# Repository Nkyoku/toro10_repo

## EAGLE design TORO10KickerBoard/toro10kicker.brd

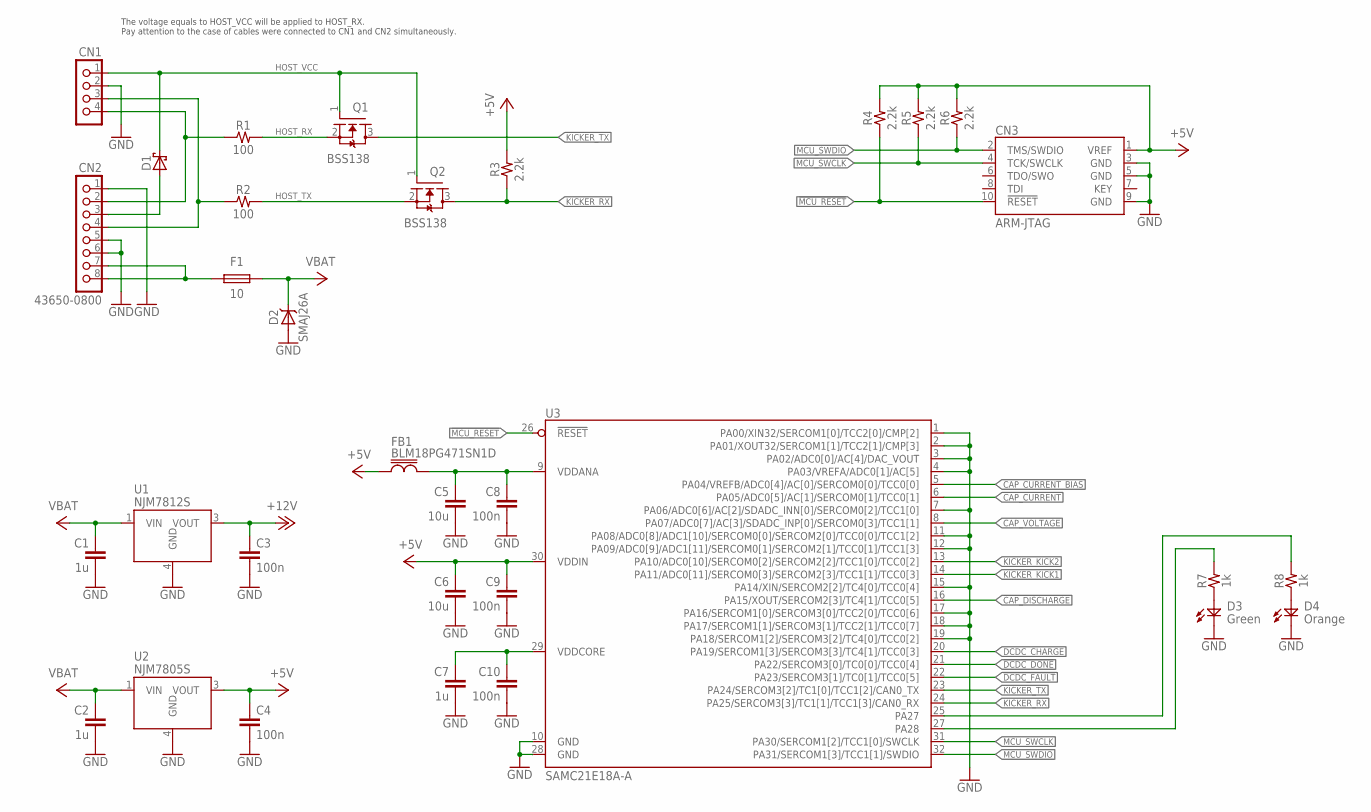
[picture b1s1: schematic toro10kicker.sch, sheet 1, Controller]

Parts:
C1, C2, C7: 1u; 1608
C3, C4, C8, C9, C10: 100n; 1608
C5, C6: 10u; 2012
CN1: PIN1X4
CN2: 43650-0800
CN3: ARM-JTAG; PIN2X5-SMT1.27
D1: SBD-1608; 1608D
D2: SMAJ26A; DO-214AC
D3: Green; 1608D
D4: Orange; 1608D
F1: 10; 3216
FB1: BLM18PG471SN1D; 1608
Q1, Q2: BSS138; SOT23-3
R1, R2: 100; 1608
R3, R4, R5, R6: 2.2k; 1608
R7, R8: 1k; 1608
U1: NJM7812S; DPAK-3
U2: NJM7805S; DPAK-3
U3: SAMC21E18A-A; QFP32-0.8

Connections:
!CAP_DISCHARGE: U3.16 (PA15/XOUT/SERCOM2[3]/TC4[1]/TCC0[5]); also elsewhere on the board
!DCDC_DONE: U3.21 (PA22/SERCOM3[0]/TC0[0]/TCC0[4]); also elsewhere on the board
!DCDC_FAULT: U3.22 (PA23/SERCOM3[1]/TC0[1]/TCC0[5]); also elsewhere on the board
!MCU_RESET: CN3.10 (!RESET), R4.1, U3.26 (!RESET)
+5V: C4.1, C6.1, C9.1, CN3.1 (VREF), FB1.1, R3.2, R4.2, R5.2, R6.2, U2.3 (VOUT), U3.30 (VDDIN); also elsewhere on the board
+12V: C3.1, U1.3 (VOUT); also elsewhere on the board
CAP_CURRENT: U3.6 (PA05/ADC0[5]/AC[1]/SERCOM0[1]/TCC0[1]); also elsewhere on the board
CAP_CURRENT_BIAS: U3.5 (PA04/VREFB/ADC0[4]/AC[0]/SERCOM0[0]/TCC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); also elsewhere on the board
CAP_VOLTAGE: U3.8 (PA07/ADC0[7]/AC[3]/SDADC_INP[0]/SERCOM0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); also elsewhere on the board
DCDC_CHARGE: U3.20 (PA19/SERCOM1[3]/SERCOM3[3]/TC4[1]/TCC0[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); also elsewhere on the board
GND: C1.2, C2.2, C3.2, C4.2, C5.2, C6.2, C7.2, C8.2, C9.2, C10.2, CN1.2, CN2.1, CN2.5, CN2.6, CN3.3 (GND), CN3.5 (GND), CN3.9 (GND), D2.A, D3.K, D4.K, U1.4 (GND), U2.4 (GND), U3.1 (PA00/XIN32/SERCOM1[0]/TCC2[0]/CMP[2]), U3.2 (PA01/XOUT32/SERCOM1[1]/TCC2[1]/CMP[3]), U3.3 (PA02/ADC0[0]/AC[4]/DAC_VOUT), U3.4 (PA03/VREFA/ADC0[1]/AC[5]), U3.7 (PA06/ADC0[6]/AC[2]/SDADC_INN[0]/SERCOM0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), U3.10 (GND), U3.11 (PA08/ADC0[8]/ADC1[10]/SERCOM0[0]/SERCOM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), U3.12 (PA09/ADC0[9]/ADC1[11]/SERCOM0[1]/SERCOM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), U3.15 (PA14/XIN/SERCOM2[2]/TC4[0]/TCC0[4]), U3.17 (PA16/SERCOM1[0]/SERCOM3[0]/TCC2[0]/TCC0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), U3.18 (PA17/SERCOM1[1]/SERCOM3[1]/TCC2[1]/TCC0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), U3.19 (PA18/SERCOM1[2]/SERCOM3[2]/TC4[0]/TCC0[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), U3.28 (GND); also elsewhere on the board
HOST_RX: Q1.2 (S), R1.2
HOST_TX: Q2.2 (S), R2.2
HOST_VCC: CN1.1, D1.K, Q1.1 (G), Q2.1 (G)
KICKER_KICK1: U3.14 (PA11/ADC0[11]/SERCOM0[3]/SERCOM2[3]/TCC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); also elsewhere on the board
KICKER_KICK2: U3.13 (PA10/ADC0[10]/SERCOM0[2]/SERCOM2[2]/TCC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); also elsewhere on the board
KICKER_RX: Q2.3 (D), R3.1, U3.24 (PA25/SERCOM3[3]/TC1[1]/TCC1[3]/CAN0_RX)
KICKER_TX: Q1.3 (D), U3.23 (PA24/SERCOM3[2]/TC1[0]/TCC1[2]/CAN0_TX)
MCU_SWCLK: CN3.4 (TCK/SWCLK), R5.1, U3.31 (PA30/SERCOM1[2]/TCC1[0]/SWCLK)
MCU_SWDIO: CN3.2 (TMS/SWDIO), R6.1, U3.32 (PA31/SERCOM1[3]/TCC1[1]/SWDIO)
unnamed: CN2.7, CN2.8, F1.1
unnamed: C5.1, C8.1, FB1.2, U3.9 (VDDANA)
unnamed: C7.1, C10.1, U3.29 (VDDCORE)
unnamed: CN1.4, CN2.2, R1.1
unnamed: CN1.3, CN2.4, R2.1
unnamed: D3.A, R7.1
unnamed: CN2.3, D1.A
unnamed: D4.A, R8.1
unnamed: R8.2, U3.25 (PA27)
unnamed: R7.2, U3.27 (PA28)
VBAT: C1.1, C2.1, D2.K, F1.2, U1.1 (VIN), U2.1 (VIN); also elsewhere on the board

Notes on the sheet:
The voltage equals to HOST_VCC will be applied to HOST_RX. Pay attention to the case of cables were connected to CN1 and CN2 simultaneously.

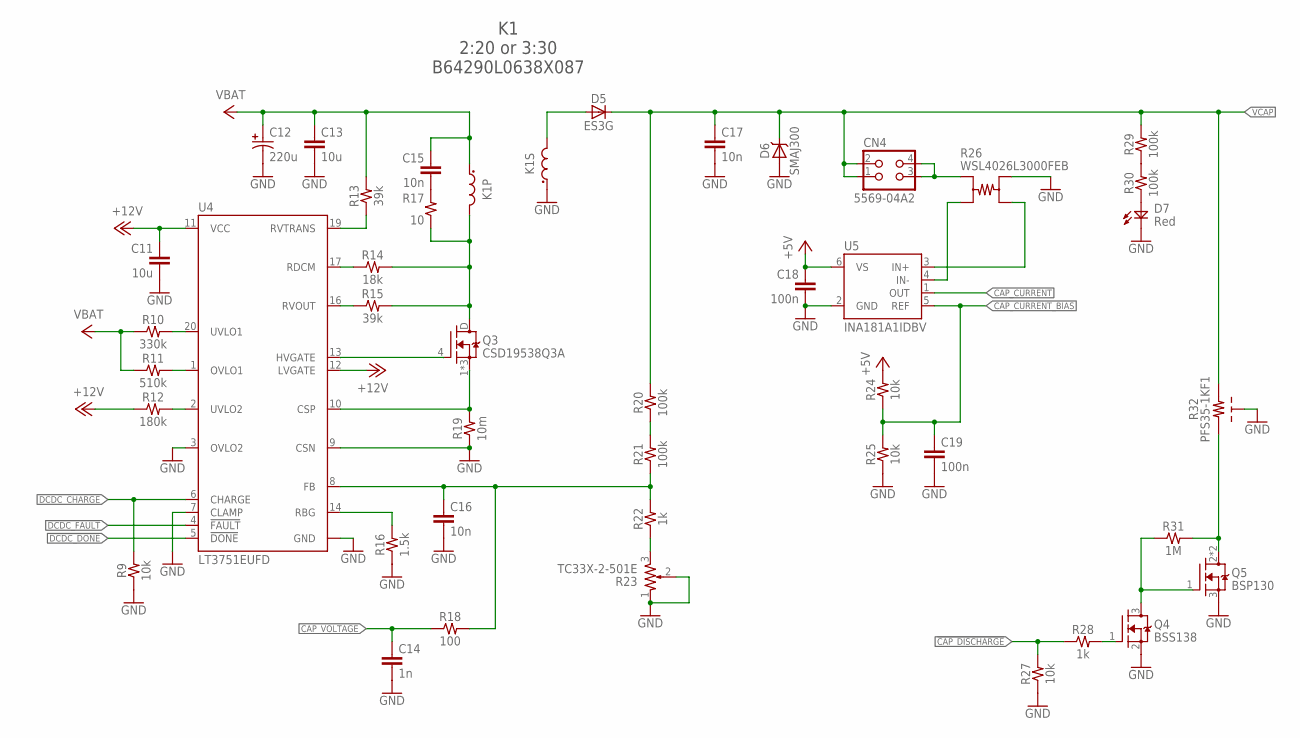
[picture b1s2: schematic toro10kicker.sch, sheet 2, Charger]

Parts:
C11: 10u; 2012
C12: 220u; E3.5-8
C13: 10u; 3225
C14: 1n; 1608
C15, C16: 10n; 1608
C17: 10n; 3225
C18, C19: 100n; 1608
CN4: 5569-04A2
D5: ES3G; DO-214AB
D6: SMAJ300; DO-214AC
D7: Red; 1608D
K1: TRANS; TRANS-23.3X12.6X7.4
Q3: CSD19538Q3A; Q3A
Q4: BSS138; SOT23-3
Q5: BSP130; SOT223
R9, R24, R25, R27: 10k; 1608
R10: 330k; 1608
R11: 510k; 1608
R12: 180k; 1608
R13, R15: 39k; 1608
R14: 18k; 1608
R16: 1.5k; 1608
R17: 10; 3216
R18: 100; 1608
R19: 10m; 3216
R20, R21, R29, R30: 100k; 3216
R22, R28: 1k; 1608
R23: TC33X-2-501E; TC33X
R26: WSL4026L3000FEB; WSL4026
R31: 1M; 3216
R32: PFS35-1KF1; D2PAK-3
U4: LT3751EUFD; QFN20-0.5-4X5
U5: INA181A1IDBV; SOT23-6

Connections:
!CAP_DISCHARGE: R27.2, R28.1; also elsewhere on the board
!DCDC_DONE: U4.5 (!DONE); also elsewhere on the board
!DCDC_FAULT: U4.4 (!FAULT); also elsewhere on the board
+5V: C18.1, R24.2, U5.6 (VS); also elsewhere on the board
+12V: C11.1, R12.1, U4.11 (VCC), U4.12 (LVGATE); also elsewhere on the board
CAP_CURRENT: U5.1 (OUT); also elsewhere on the board
CAP_CURRENT_BIAS: C19.1, R24.1, R25.2, U5.5 (REF); also elsewhere on the board
CAP_VOLTAGE: C14.1, R18.1; also elsewhere on the board
DCDC_CHARGE: R9.2, U4.6 (CHARGE); also elsewhere on the board
GND: C11.2, C12.N, C13.2, C14.2, C16.2, C17.2, C18.2, C19.2, D6.A, D7.K, K1.2A (1), Q4.2 (S), Q5.3 (S), R9.1, R16.1, R19.1, R23.1 (A), R23.2 (W), R25.1, R26.1A, R27.1, R32.4 (S), U4.3 (OVLO2), U4.7 (CLAMP), U4.9 (CSN), U4.PAD (GND), U5.2 (GND); also elsewhere on the board
unnamed: Q3.1 (S), Q3.2 (S), Q3.3 (S), R19.2, U4.10 (CSP)
unnamed: R10.2, U4.20 (UVLO1)
unnamed: R11.2, U4.1 (OVLO1)
unnamed: R12.2, U4.2 (UVLO2)
unnamed: Q5.2 (D), Q5.4 (D), R31.2, R32.1
unnamed: R14.1, U4.17 (RDCM)
unnamed: R15.1, U4.16 (RVOUT)
unnamed: K1.1B (2), Q3.D, R14.2, R15.2, R17.1
unnamed: R13.1, U4.19 (RVTRANS)
unnamed: Q3.4 (G), U4.13 (HVGATE)
unnamed: R22.1, R23.3 (B)
unnamed: C16.1, R18.2, R21.1, R22.2, U4.8 (FB)
unnamed: R16.2, U4.14 (RBG)
unnamed: CN4.3, CN4.4, R26.2A
unnamed: R29.1, R30.2
unnamed: D5.A, K1.2B (2)
unnamed: R20.1, R21.2
unnamed: Q4.3 (D), Q5.1 (G), R31.1
unnamed: C15.2, R17.2
unnamed: Q4.1 (G), R28.2
unnamed: D7.A, R30.1
unnamed: R26.2B, U5.4 (IN-)
unnamed: R26.1B, U5.3 (IN+)
VBAT: C12.P, C13.1, C15.1, K1.1A (1), R10.1, R11.1, R13.2; also elsewhere on the board
VCAP: C17.1, CN4.1, CN4.2, D5.K, D6.K, R20.2, R29.2, R32.3 (2); also elsewhere on the board

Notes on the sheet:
K1 2:20 or 3:30 B64290L0638X087

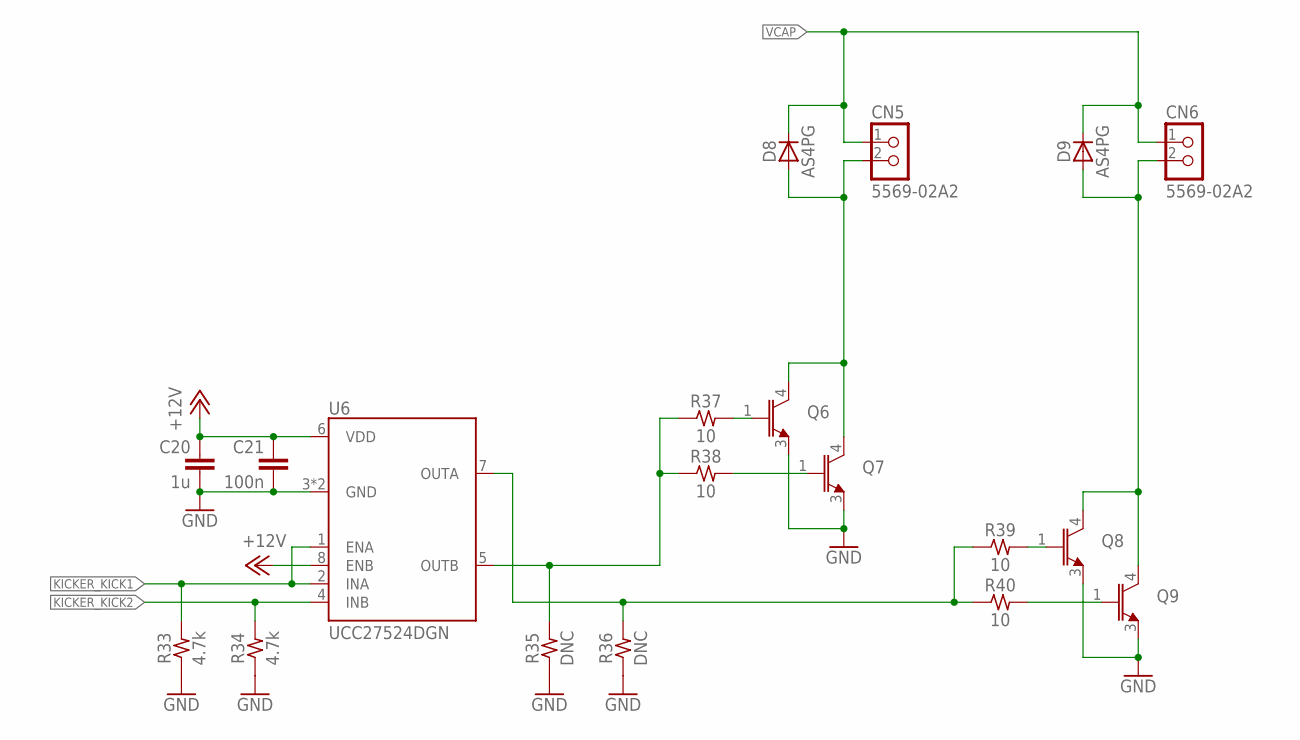
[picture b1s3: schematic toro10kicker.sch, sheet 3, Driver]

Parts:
C20: 1u; 1608
C21: 100n; 1608
CN5, CN6: 5569-02A2
D8, D9: AS4PG; SMPC
Q6, Q7, Q8, Q9: IGBT-N-D2PAK; D2PAK-3
R33, R34: 4.7k; 1608
R35, R36: DNC; 1608
R37, R38, R39, R40: 10; 2012
U6: UCC27524DGN; MSOP8-PAD

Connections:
+12V: C20.1, C21.1, U6.6 (VDD), U6.8 (ENB); also elsewhere on the board
GND: C20.2, C21.2, Q6.3 (E), Q7.3 (E), Q8.3 (E), Q9.3 (E), R33.1, R34.1, R35.1, R36.1, U6.3 (GND), U6.PAD (GND); also elsewhere on the board
KICKER_KICK1: R33.2, U6.1 (ENA), U6.2 (INA); also elsewhere on the board
KICKER_KICK2: R34.2, U6.4 (INB); also elsewhere on the board
unnamed: CN5.2, D8.1 (A), D8.2 (A), Q6.4 (C), Q7.4 (C)
unnamed: CN6.2, D9.1 (A), D9.2 (A), Q8.4 (C), Q9.4 (C)
unnamed: Q6.1 (G), R37.2
unnamed: Q7.1 (G), R38.2
unnamed: R35.2, R37.1, R38.1, U6.5 (OUTB)
unnamed: Q8.1 (G), R39.2
unnamed: Q9.1 (G), R40.2
unnamed: R36.2, R39.1, R40.1, U6.7 (OUTA)
VCAP: CN5.1, CN6.1, D8.K, D9.K; also elsewhere on the board

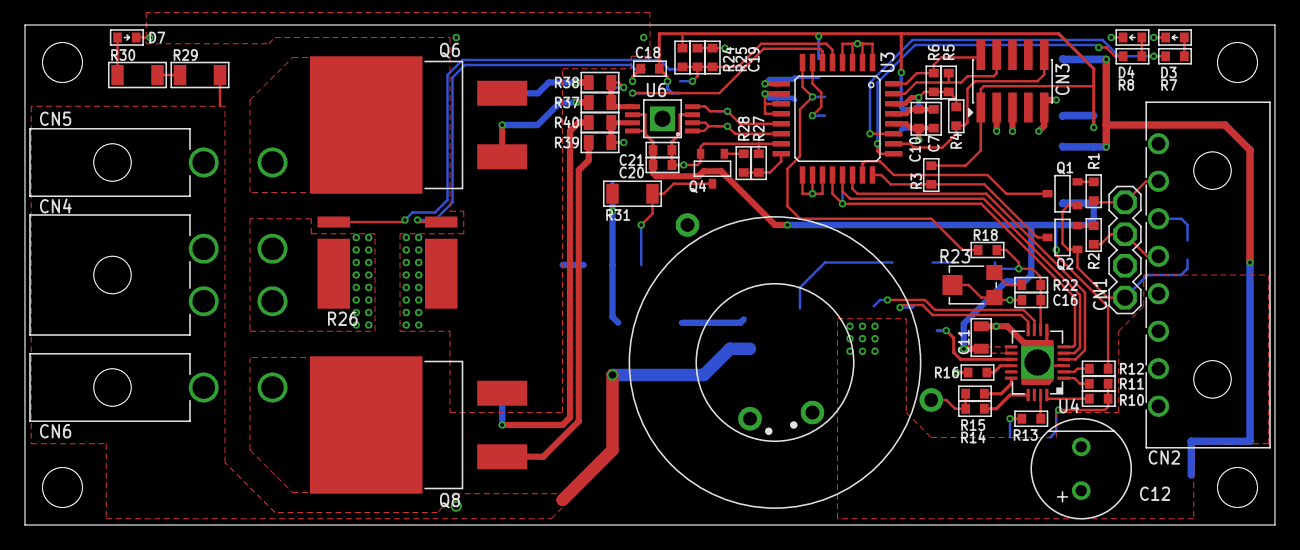
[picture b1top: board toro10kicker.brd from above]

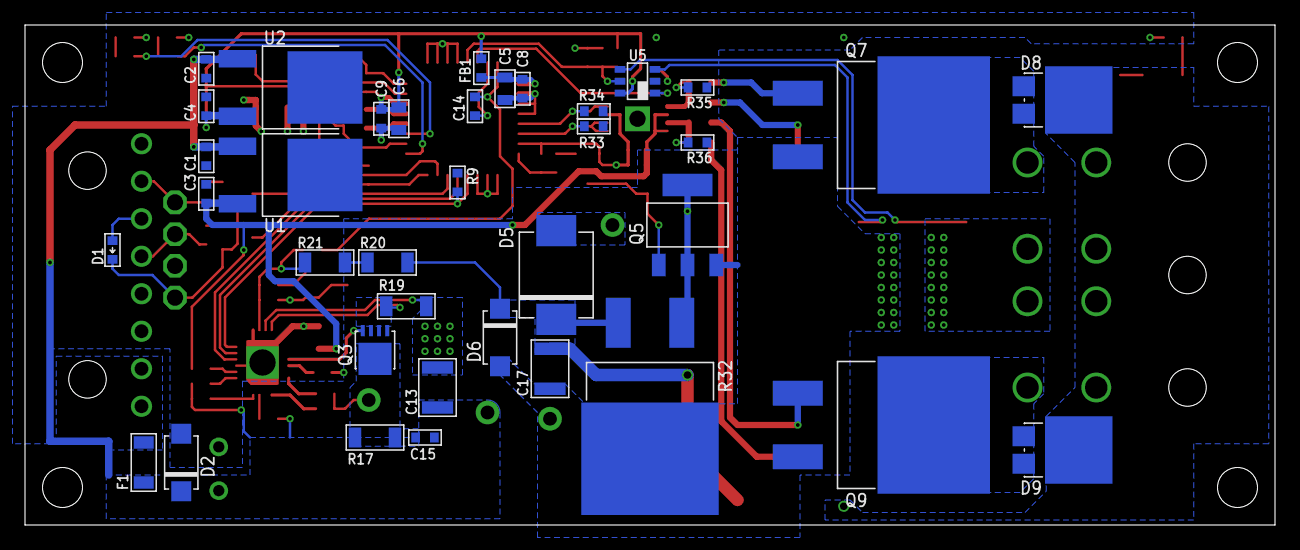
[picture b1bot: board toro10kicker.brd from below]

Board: 2 copper layers, 100.0 x 40.0 mm, 94 parts (37 on the bottom side), 63 nets.

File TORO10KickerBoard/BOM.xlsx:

Device | Model Number | Value | Package | Qty | Parts
Resistor | WSL4026L3000FEB | 0.3mΩ | WSL4026 | 1 | R26
Resistor |  | 10mΩ | 3216 | 1 | R19
Resistor |  | 10Ω | 2012 | 4 | R37, R38, R39, R40
Resistor |  | 10Ω | 3216 | 1 | R17
Resistor |  | 100Ω | 1608 | 3 | R1, R2, R18
Resistor |  | 1kΩ | 1608 | 4 | R7, R8, R22, R28
Resistor | PFS35-1KF1 | 1kΩ | D2PAK-3 | 1 | R32
Resistor |  | 1.5kΩ | 1608 | 1 | R16
Resistor |  | 2.2kΩ | 1608 | 4 | R3, R4, R5, R6
Resistor |  | 4.7kΩ | 1608 | 2 | R33, R34
Resistor |  | 10kΩ | 1608 | 4 | R9, R24, R25, R27
Resistor |  | 18kΩ ±1% | 1608 | 1 | R14
Resistor |  | 39kΩ ±1% | 1608 | 2 | R13, R15
Resistor | KTR18EZPF1003 | 100kΩ ±1% | 3216 | 4 | R20, R21, R29, R30
Resistor |  | 180kΩ ±1% | 1608 | 1 | R12
Resistor |  | 330kΩ ±1% | 1608 | 1 | R10
Resistor |  | 510kΩ ±1% | 1608 | 1 | R11
Resistor | KTR18EZPF1004 | 1MΩ | 3216 | 1 | R31
Resistor |  | Do Not Mount | 1608 | 2 | R35, R36
Potentiometer | TC33X-2-501E | 500Ω | TC33X | 1 | R23
Ceramic Capacitor |  | 1nF | 1608 | 1 | C14
Ceramic Capacitor |  | 10nF | 1608 | 2 | C15, C16
Ceramic Capacitor | GRM31BR72J103KW01L | 10nF 630V | 3225 | 1 | C17
Ceramic Capacitor |  | 100nF | 1608 | 8 | C3, C4, C8, C9, C10, C18, C19, C21
Ceramic Capacitor |  | 1uF | 1608 | 4 | C1, C2, C7, C20
Ceramic Capacitor | GRM21BB31E106KA | 10uF 16V | 2012 | 3 | C5, C6, C11
Ceramic Capacitor | GRM32ER7YA106KA12 | 10uF 35V | 3225 | 1 | C13
Aluminum Capacitor | 35ZLH220MEFCCT8X11.5 | 220uF | φ8mm | 1 | C12
Transformer | B64290L0638X087 |  | TRANS-23.3X12.6X7.4 | 1 | K1
Fuse | 0501010.WR | 10A | 3216 | 1 | F1
Ferrite Bead | BLM18PG471SN1D |  | 1608 | 1 | FB1
Silicon Diode | ES3G-E3/57T |  | DO-214AB | 1 | D5
Silicon Diode | AS4PG-M3/86A |  | SMPC | 2 | D8, D9
Schottky Diode | RB520S-30 |  | 1608 | 1 | D1
TVS Diode | SMAJ26A |  | DO-214AC | 1 | D2
TVS Diode | SMAJ300A |  | DO-214AC | 1 | D6
LED |  | Red | 1608 | 1 | D7
LED |  | Green | 1608 | 2 | D3
LED |  | Orange | 1608 | 2 | D4
Nch MOSFET | BSS138 |  | SOT23-3 | 3 | Q1, Q2, Q4
Nch MOSFET | BSP130,115 |  | SOT223 | 1 | Q5
Nch MOSFET | CSD19538Q3A |  | Q3A | 1 | Q3
IGBT |  |  | D2PAK-3 | 4 | Q6, Q7, Q8, Q9
Linear Regulator | NJM7805SDL1 |  | DPAK-3 | 1 | U2
Linear Regulator | NJM7812SDL1 |  | DPAK-3 | 1 | U1
Boost Regulator | LT3751EUFD#PBF |  | QFN20-0.5-4X5 | 1 | U4
Current Sense Amplifier | INA181A1IDBVT |  | SOT23-6 | 1 | U5
Gate Driver | UCC27524DGNR, UCC27524ADGNR |  | MSOP8-PAD | 1 | U6
Microcontroller | ATSAMC21E18A-AUT |  | QFP32-0.8 | 1 | U3
Header | 0436500800 |  | 43650-0800 | 1 | CN2
Header | 0039301020 |  | 5569-02A2 | 2 | CN5, CN6
Header | 0039301040 |  | 5569-04A2 | 1 | CN4
Pin Header | Pin Header 1x4 2.54mm Pitch |  | PIN1X4 | 1 | CN1
Pin Header | Pin Header 2x5 1.27mm Pitch |  | PIN2X5-SMT1.27 | 1 | CN3

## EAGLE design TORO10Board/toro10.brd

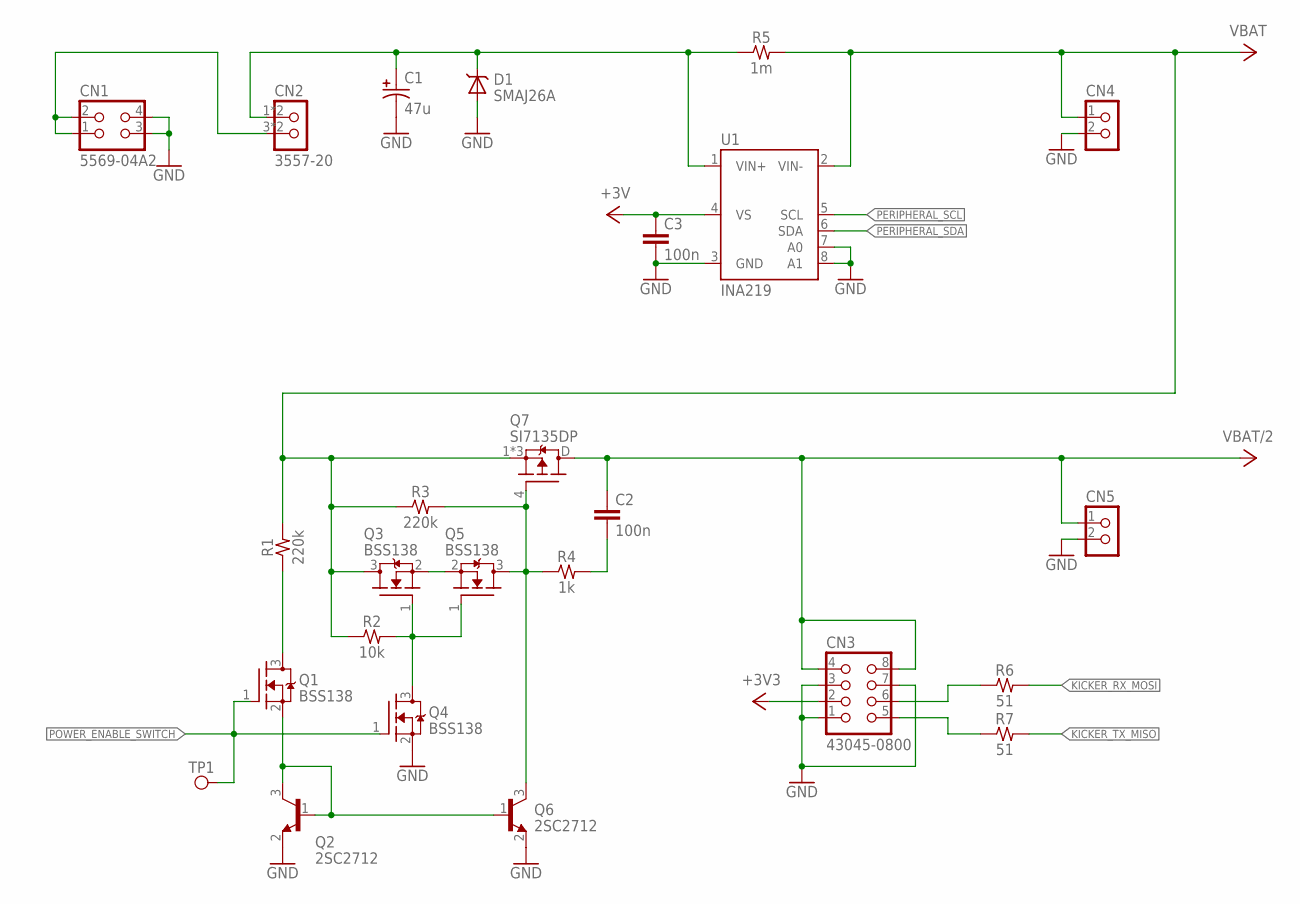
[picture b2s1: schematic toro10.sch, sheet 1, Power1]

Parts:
C1: 47u; E2-5
C2, C3: 100n; 1608
CN1: 5569-04A2
CN2: 3557-20; 3557
CN3: 43045-0800
CN4, CN5: PIN1X2
D1: SMAJ26A; DO-214AC
Q1, Q3, Q4, Q5: BSS138; SOT23-3
Q2, Q6: 2SC2712; SOT23-3
Q7: SI7135DP; POWERPAK-SO-8-S
R1, R3: 220k; 1608
R2: 10k; 1608
R4: 1k; 1608
R5: 1m; WSLF2512
R6, R7: 51; 1608
TP1: TESTPAD-SMT
U1: INA219; SOT23-8

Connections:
+3V: C3.1, U1.4 (VS); also elsewhere on the board
+3V3: CN3.2; also elsewhere on the board
GND: C1.N, C3.2, CN1.3, CN1.4, CN3.1, CN3.3, CN3.7, CN4.2, CN5.2, D1.A, Q2.2 (E), Q4.2 (S), Q6.2 (E), U1.3 (GND), U1.7 (A0), U1.8 (A1); also elsewhere on the board
KICKER_RX_MOSI: R6.2; also elsewhere on the board
KICKER_TX_MISO: R7.2; also elsewhere on the board
unnamed: CN1.1, CN1.2, CN2.3 (2), CN2.4 (2)
unnamed: Q3.2 (S), Q5.2 (S)
unnamed: Q3.1 (G), Q4.3 (D), Q5.1 (G), R2.2
unnamed: Q1.2 (S), Q2.1 (B), Q2.3 (C), Q6.1 (B)
unnamed: Q5.3 (D), Q6.3 (C), Q7.4 (G), R3.2, R4.1
unnamed: C2.2, R4.2
unnamed: Q1.3 (D), R1.1
unnamed: C1.P, CN2.1, CN2.2 (1), D1.K, R5.1, U1.1 (VIN+)
unnamed: CN3.6, R6.1
unnamed: CN3.5, R7.1
PERIPHERAL_SCL: U1.5 (SCL); also elsewhere on the board
PERIPHERAL_SDA: U1.6 (SDA); also elsewhere on the board
POWER_ENABLE_SWITCH: Q1.1 (G), Q4.1 (G), TP1.1; also elsewhere on the board
VBAT: CN4.1, Q3.3 (D), Q7.1 (S), Q7.2 (S), Q7.3 (S), R1.2, R2.1, R3.1, R5.2, U1.2 (VIN-); also elsewhere on the board
VBAT/2: C2.1, CN3.4, CN3.8, CN5.1, Q7.D; also elsewhere on the board

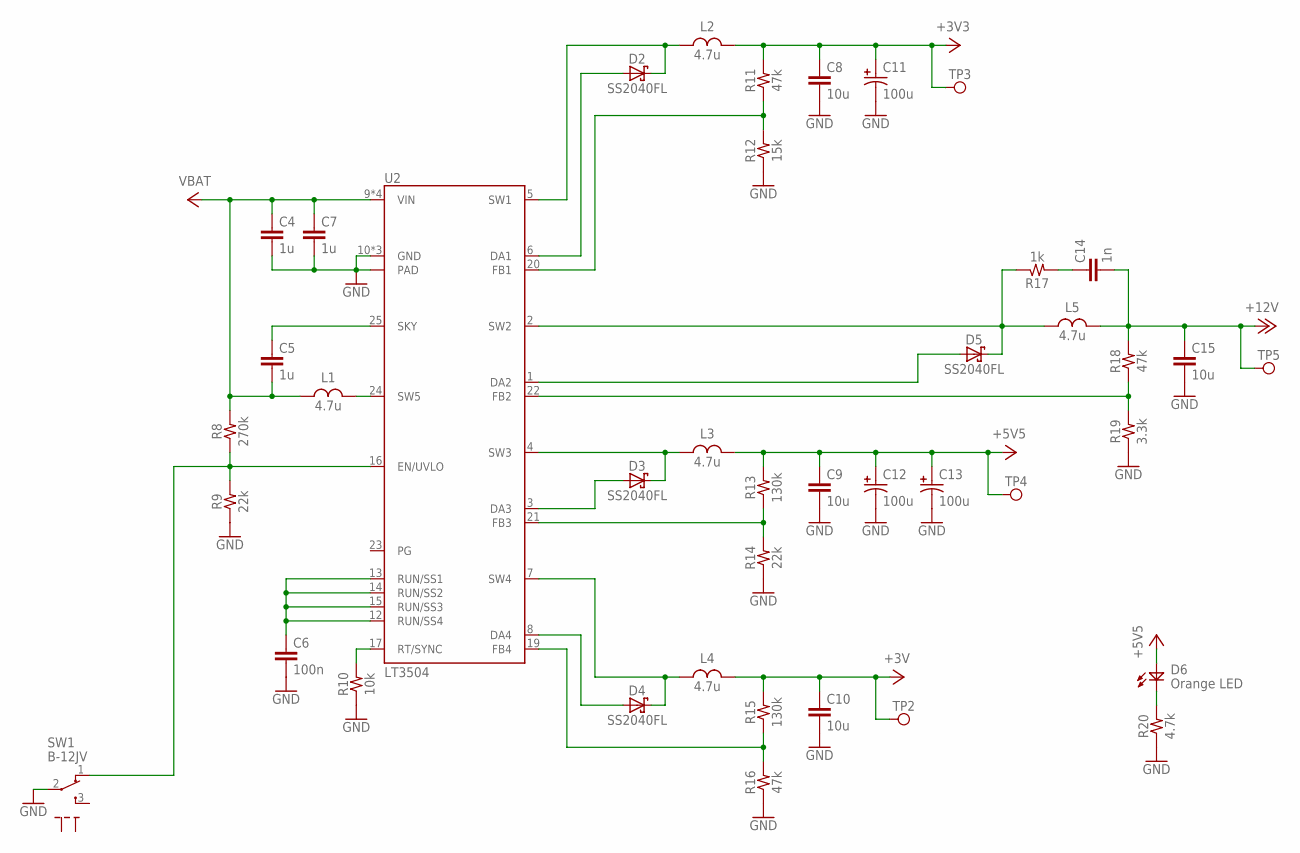
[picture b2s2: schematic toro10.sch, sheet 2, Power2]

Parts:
C4, C5, C7: 1u; 1608
C6: 100n; 1608
C8, C9, C10, C15: 10u; 2012
C11, C12, C13: 100u; E2-5
C14: 1n; 1608
D2, D3, D4, D5: SS2040FL; SOD123
D6: Orange LED; 1608D
L1, L2, L3, L4, L5: 4.7u; MAMK2520
R8: 270k; 1608
R9, R14: 22k; 1608
R10: 10k; 1608
R11, R16, R18: 47k; 1608
R12: 15k; 1608
R13, R15: 130k; 1608
R17: 1k; 1608
R19: 3.3k; 1608
R20: 4.7k; 1608
SW1: B-12JV
TP2, TP3, TP4, TP5: TESTPAD-TH
U2: LT3504; QFN28-0.5

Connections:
+3V: C10.1, L4.2, R15.2, TP2.1; also elsewhere on the board
+3V3: C8.1, C11.P, L2.2, R11.2, TP3.1; also elsewhere on the board
+5V5: C9.1, C12.P, C13.P, D6.A, L3.2, R13.2, TP4.1; also elsewhere on the board
+12V: C14.2, C15.1, L5.2, R18.2, TP5.1; also elsewhere on the board
GND: C4.2, C6.2, C7.2, C8.2, C9.2, C10.2, C11.N, C12.N, C13.N, C15.2, R9.1, R10.1, R12.1, R14.1, R16.1, R19.1, R20.1, SW1.2 (COM), U2.10 (GND), U2.18 (GND), U2.27 (GND), U2.PAD; also elsewhere on the board
unnamed: R18.1, R19.2, U2.22 (FB2)
unnamed: L1.2, U2.24 (SW5)
unnamed: C6.1, U2.12 (RUN/SS4), U2.13 (RUN/SS1), U2.14 (RUN/SS2), U2.15 (RUN/SS3)
unnamed: R10.2, U2.17 (RT/SYNC)
unnamed: C5.1, U2.25 (SKY)
unnamed: D2.K, L2.1, U2.5 (SW1)
unnamed: D5.K, L5.1, R17.1, U2.2 (SW2)
unnamed: R8.1, R9.2, SW1.1 (A), U2.16 (EN/UVLO)
unnamed: R15.1, R16.2, U2.19 (FB4)
unnamed: R11.1, R12.2, U2.20 (FB1)
unnamed: D5.A, U2.1 (DA2)
unnamed: R13.1, R14.2, U2.21 (FB3)
unnamed: D3.A, U2.3 (DA3)
unnamed: D3.K, L3.1, U2.4 (SW3)
unnamed: D4.K, L4.1, U2.7 (SW4)
unnamed: D4.A, U2.8 (DA4)
unnamed: C14.1, R17.2
unnamed: D2.A, U2.6 (DA1)
unnamed: D6.K, R20.2
VBAT: C4.1, C5.2, C7.1, L1.1, R8.2, U2.9 (VIN), U2.11 (VIN), U2.26 (VIN), U2.28 (VIN); also elsewhere on the board

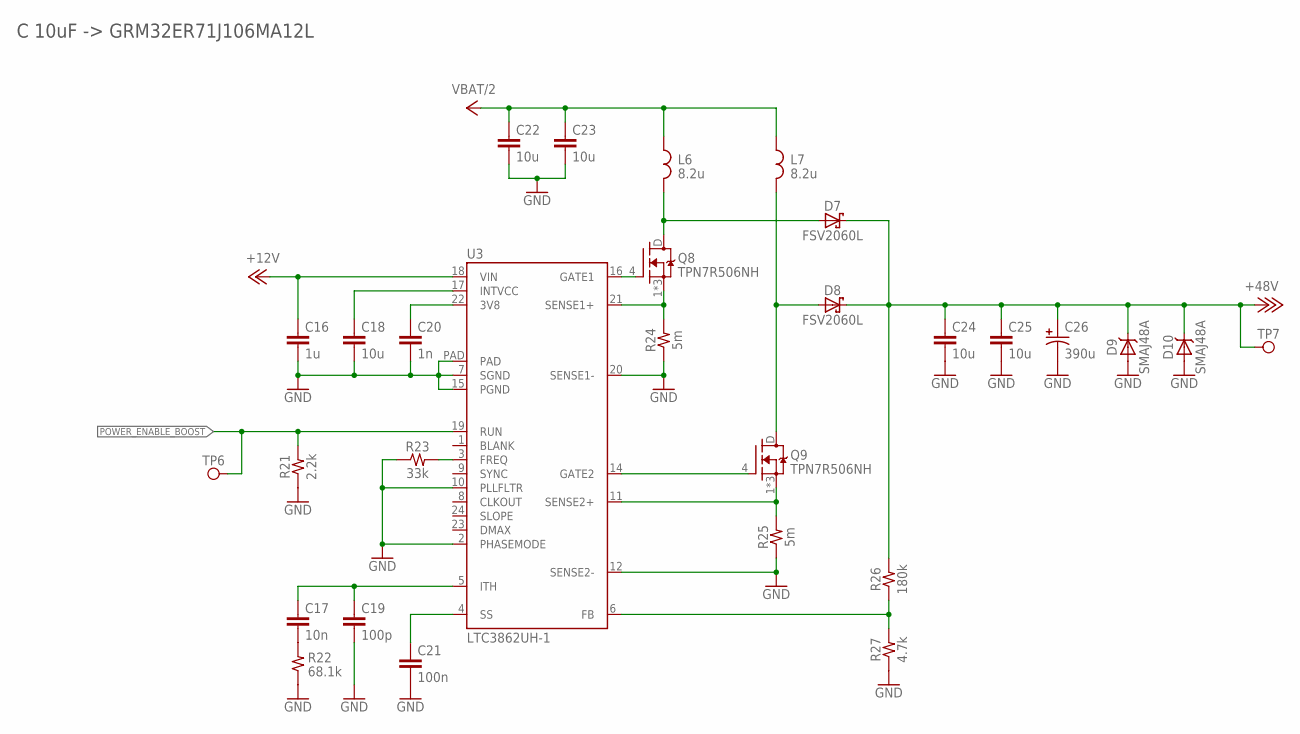
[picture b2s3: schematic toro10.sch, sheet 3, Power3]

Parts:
C16: 1u; 1608
C17: 10n; 1608
C18: 10u; 2012
C19: 100p; 1608
C20: 1n; 1608
C21: 100n; 1608
C22, C23, C24, C25: 10u; 3225
C26: 390u; E7.5-18
D7, D8: FSV2060L; TO-277-3
D9, D10: SMAJ48A; DO-214AC
L6, L7: 8.2u; L-VISHAY-ER
Q8, Q9: TPN7R506NH; TSON-8_3.3
R21: 2.2k; 1608
R22: 68.1k; 1608
R23: 33k; 1608
R24, R25: 5m; 3216WL
R26: 180k; 1608
R27: 4.7k; 1608
TP6, TP7: TESTPAD-SMT
U3: LTC3862UH-1; QFN24-0.65

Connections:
+12V: C16.1, U3.18 (VIN); also elsewhere on the board
+48V: C24.1, C25.1, C26.P, D7.3 (K), D8.3 (K), D9.K, D10.K, R26.2, TP7.1; also elsewhere on the board
GND: C16.2, C18.2, C19.2, C20.2, C21.2, C22.2, C23.2, C24.2, C25.2, C26.N, D9.A, D10.A, R21.1, R22.1, R23.1, R24.1, R25.1, R27.1, U3.2 (PHASEMODE), U3.7 (SGND), U3.10 (PLLFLTR), U3.12 (SENSE2-), U3.15 (PGND), U3.20 (SENSE1-), U3.PAD; also elsewhere on the board
unnamed: Q8.1 (S), Q8.2 (S), Q8.3 (S), R24.2, U3.21 (SENSE1+)
unnamed: C18.1, U3.17 (INTVCC)
unnamed: Q8.4 (G), U3.16 (GATE1)
unnamed: D7.1 (A), D7.2 (A), L6.2, Q8.D
unnamed: Q9.1 (S), Q9.2 (S), Q9.3 (S), R25.2, U3.11 (SENSE2+)
unnamed: C20.1, U3.22 (3V8)
unnamed: Q9.4 (G), U3.14 (GATE2)
unnamed: D8.1 (A), D8.2 (A), L7.2, Q9.D
unnamed: R26.1, R27.2, U3.6 (FB)
unnamed: C21.1, U3.4 (SS)
unnamed: C17.2, R22.2
unnamed: C17.1, C19.1, U3.5 (ITH)
unnamed: R23.2, U3.3 (FREQ)
POWER_ENABLE_BOOST: R21.2, TP6.1, U3.19 (RUN); also elsewhere on the board
VBAT/2: C22.1, C23.1, L6.1, L7.1; also elsewhere on the board

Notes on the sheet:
C 10uF -> GRM32ER71J106MA12L

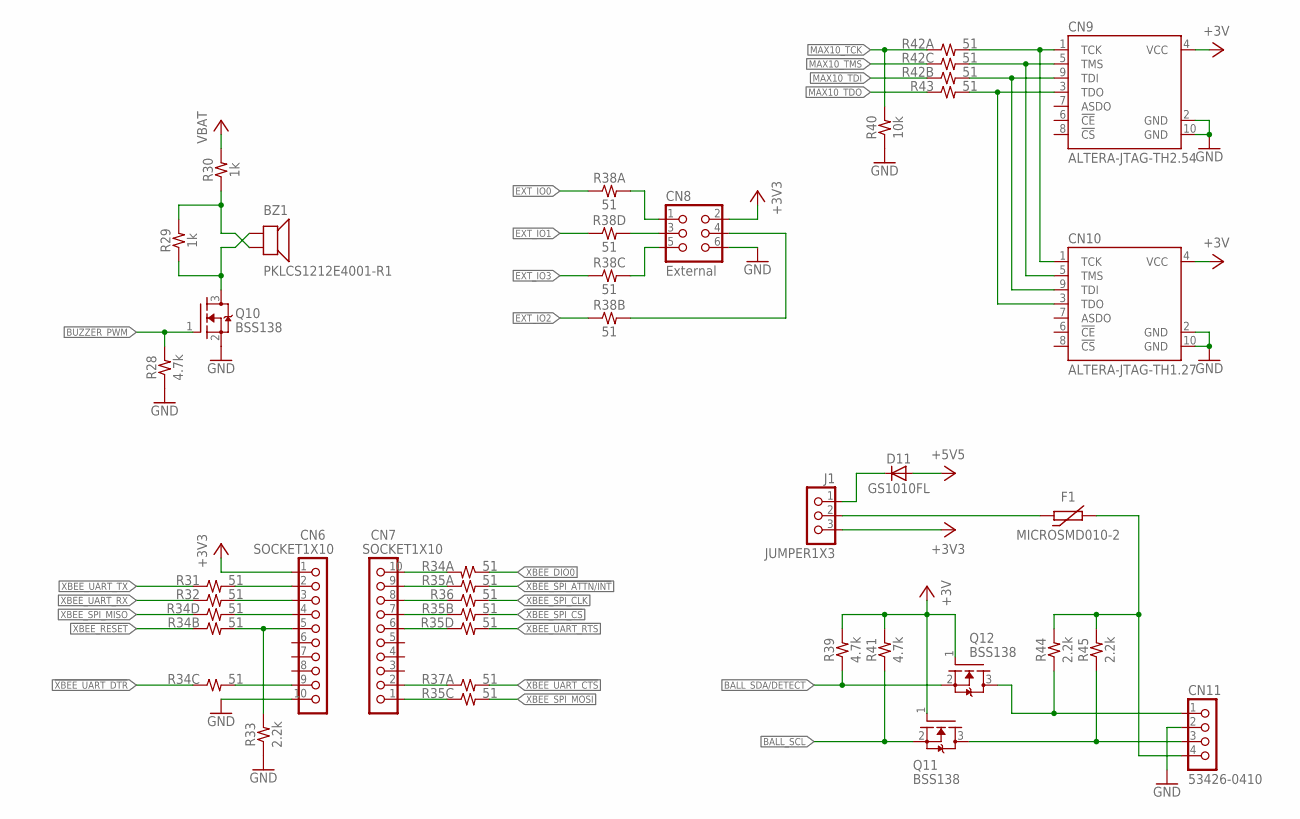
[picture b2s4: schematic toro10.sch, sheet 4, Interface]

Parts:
BZ1: PKLCS1212E4001-R1; PKLCS1212
CN6, CN7: SOCKET1X10; SOCKET1X10-TH2.0
CN8: External; PIN2X3
CN9: ALTERA-JTAG-TH2.54; PIN2X5
CN10: ALTERA-JTAG-TH1.27; PIN2X5-1.27
CN11: 53426-0410; 53426-04
D11: GS1010FL; SOD123
F1: MICROSMD010-2; 3225
J1: JUMPER1X3; PIN1X3
Q10, Q11, Q12: BSS138; SOT23-3
R28, R39, R41: 4.7k; 1608
R29, R30: 1k; 1608
R31, R32, R36, R43: 51; 1608
R33, R44, R45: 2.2k; 1608
R34, R35, R37, R38, R42: 51; 1608-4A
R40: 10k; 1608

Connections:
!XBEE_RESET: R34.B1 (1); also elsewhere on the board
!XBEE_SPI_ATTN/INT: R35.A2 (2); also elsewhere on the board
!XBEE_SPI_CS: R35.B2 (2); also elsewhere on the board
!XBEE_UART_CTS: R37.A2 (2); also elsewhere on the board
!XBEE_UART_DTR: R34.C1 (1); also elsewhere on the board
!XBEE_UART_RTS: R35.D2 (2); also elsewhere on the board
+3V: CN9.4 (VCC), CN10.4 (VCC), Q11.1 (G), Q12.1 (G), R39.2, R41.2; also elsewhere on the board
+3V3: CN6.1, CN8.2, J1.3; also elsewhere on the board
+5V5: D11.A; also elsewhere on the board
BALL_SCL: Q11.2 (S), R41.1; also elsewhere on the board
BALL_SDA/DETECT: Q12.2 (S), R39.1; also elsewhere on the board
BUZZER_PWM: Q10.1 (G), R28.2; also elsewhere on the board
EXT_IO0: R38.A1 (1); also elsewhere on the board
EXT_IO1: R38.D1 (1); also elsewhere on the board
EXT_IO2: R38.B1 (1); also elsewhere on the board
EXT_IO3: R38.C1 (1); also elsewhere on the board
GND: CN6.10, CN8.6, CN9.2 (GND), CN9.10 (GND), CN10.2 (GND), CN10.10 (GND), CN11.2, Q10.2 (S), R28.1, R33.1, R40.1; also elsewhere on the board
MAX10_TCK: R40.2, R42.A1 (1); also elsewhere on the board
MAX10_TDI: R42.B1 (1); also elsewhere on the board
MAX10_TDO: R43.1; also elsewhere on the board
MAX10_TMS: R42.C1 (1); also elsewhere on the board
unnamed: CN9.5 (TMS), CN10.5 (TMS), R42.C2 (2)
unnamed: CN9.9 (TDI), CN10.9 (TDI), R42.B2 (2)
unnamed: CN9.1 (TCK), CN10.1 (TCK), R42.A2 (2)
unnamed: BZ1.1, Q10.3 (D), R29.1
unnamed: CN9.3 (TDO), CN10.3 (TDO), R43.2
unnamed: CN8.1, R38.A2 (2)
unnamed: BZ1.2, R29.2, R30.1
unnamed: CN8.3, R38.D2 (2)
unnamed: CN8.5, R38.C2 (2)
unnamed: CN8.4, R38.B2 (2)
unnamed: CN11.4, F1.2, R44.2, R45.2
unnamed: D11.K, J1.1
unnamed: F1.1, J1.2
unnamed: CN11.3, Q11.3 (D), R45.1
unnamed: CN11.1, Q12.3 (D), R44.1
unnamed: CN7.2, R37.A1 (1)
unnamed: CN7.9, R35.A1 (1)
unnamed: CN7.7, R35.B1 (1)
unnamed: CN7.6, R35.D1 (1)
unnamed: CN7.1, R35.C1 (1)
unnamed: CN7.10, R34.A2 (2)
unnamed: CN6.4, R34.D2 (2)
unnamed: CN6.5, R33.2, R34.B2 (2)
unnamed: CN6.9, R34.C2 (2)
unnamed: CN7.8, R36.1
unnamed: CN6.2, R31.2
unnamed: CN6.3, R32.2
VBAT: R30.2; also elsewhere on the board
XBEE_DIO0: R34.A1 (1); also elsewhere on the board
XBEE_SPI_CLK: R36.2; also elsewhere on the board
XBEE_SPI_MISO: R34.D1 (1); also elsewhere on the board
XBEE_SPI_MOSI: R35.C2 (2); also elsewhere on the board
XBEE_UART_RX: R32.1; also elsewhere on the board
XBEE_UART_TX: R31.1; also elsewhere on the board
